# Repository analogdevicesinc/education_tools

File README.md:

# ADI Educational Content

[Analog Devices Inc.](https://www.analog.com/en/index.html)

Resource files for applications/examples with Active Learning Modules [ADALM1000](https://www.analog.com/en/design-center/evaluation-hardware-and-software/evaluation-boards-kits/adalm1000.html), [ADALM2000](https://www.analog.com/en/design-center/evaluation-hardware-and-software/evaluation-boards-kits/adalm2000.html), [ADALM-PLUTO](https://www.analog.com/en/design-center/evaluation-hardware-and-software/evaluation-boards-kits/adalm-pluto.html) and [ADALP2000](https://www.analog.com/en/design-center/evaluation-hardware-and-software/evaluation-boards-kits/EVAL-ADALP2000.html) Parts Kit.

Most of the files are linked as archives to the activities available in the [Analog Devices Engineering University Program](https://wiki.analog.com/university).

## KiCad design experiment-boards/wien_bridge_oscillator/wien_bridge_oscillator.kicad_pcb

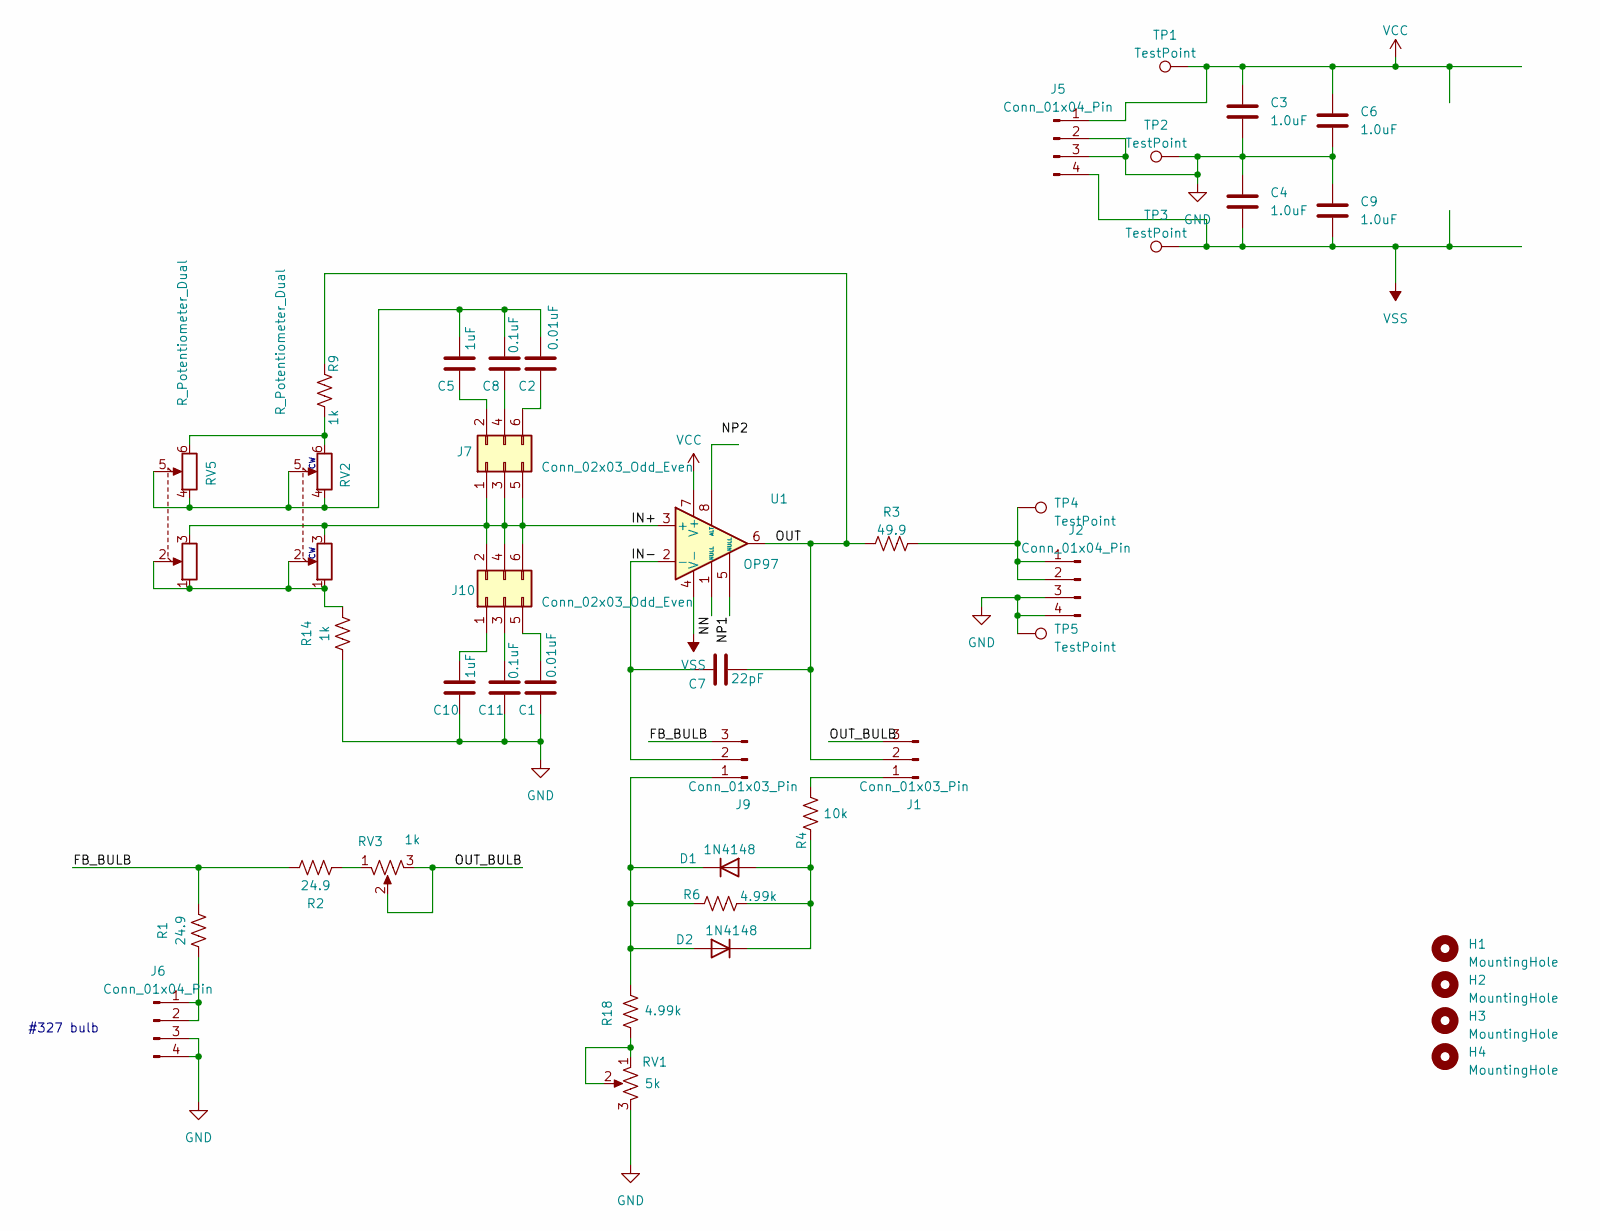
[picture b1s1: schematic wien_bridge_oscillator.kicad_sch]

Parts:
C1, C2: 0.01uF; C_Rect_L7.0mm_W3.5mm_P2.50mm_P5.00mm
C3, C4, C6, C9: 1.0uF; C_Rect_L7.0mm_W3.5mm_P2.50mm_P5.00mm
C5, C10: 1uF; C_Rect_L7.0mm_W3.5mm_P2.50mm_P5.00mm
C7: 22pF; C_Rect_L7.0mm_W3.5mm_P2.50mm_P5.00mm
C8, C11: 0.1uF; C_Rect_L7.0mm_W3.5mm_P2.50mm_P5.00mm
D1, D2: 1N4148; D_DO-35_SOD27_P7.62mm_Horizontal
H1, H2, H3, H4: MountingHole; MountingHole_3.2mm_M3
J1, J9: Conn_01x03_Pin; PinHeader_1x03_P2.54mm_Vertical
J2, J5, J6: Conn_01x04_Pin; PinHeader_1x04_P2.54mm_Vertical
J7, J10: Conn_02x03_Odd_Even; PinHeader_2x03_P2.54mm_Vertical
R1, R2: 24.9; R_Axial_DIN0207_L6.3mm_D2.5mm_P10.16mm_Horizontal
R3: 49.9; R_Axial_DIN0207_L6.3mm_D2.5mm_P10.16mm_Horizontal
R4: 10k; R_Axial_DIN0207_L6.3mm_D2.5mm_P10.16mm_Horizontal
R6, R18: 4.99k; R_Axial_DIN0207_L6.3mm_D2.5mm_P10.16mm_Horizontal
R9, R14: 1k; R_Axial_DIN0207_L6.3mm_D2.5mm_P10.16mm_Horizontal
RV1: 5k; Potentiometer_Bourns_3386F_Vertical
RV2: R_Potentiometer_Dual; Potentiometer_Bourns_3386F_Vertical
RV3: 1k; Potentiometer_Bourns_3386F_Vertical
RV5: R_Potentiometer_Dual; Potentiometer_Bourns_PRS12R-4x_Dual_Vertical
TP1, TP2, TP3, TP4, TP5: TestPoint; TestPoint_Keystone_5005-5009_Compact
U1: OP97; DIP-8_W7.62mm

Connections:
/FB_BULB: J9.3, R1.2, R2.2
/IN+: J7.1, J7.3, J7.5, J10.2, J10.4, J10.6, RV2.3, RV5.3, U1.3 (+)
/IN-: C7.1, J9.2, U1.2 (-)
/NN: U1.1 (NULL)
/NP1: U1.5 (NULL)
/OUT: C7.2, J1.2, R3.1, R9.1, U1.6
/OUT_BULB: J1.3, RV3.2, RV3.3
GND: C1.1, C3.2, C4.1, C6.2, C9.1, C10.1, C11.1, J2.3, J2.4, J5.2, J5.3, J6.3, J6.4, R14.1, RV1.3, TP2.1, TP5.1
unnamed: C2.2, C5.2, C8.2, RV2.4, RV2.5, RV5.4, RV5.5
unnamed: D1.2 (A), D2.1 (K), R4.1, R6.2
unnamed: D1.1 (K), D2.2 (A), J9.1, R6.1, R18.2
unnamed: J1.1, R4.2
unnamed: J2.1, J2.2, R3.2, TP4.1
unnamed: J6.1, J6.2, R1.1
unnamed: C5.1, J7.2
unnamed: C8.1, J7.4
unnamed: C2.1, J7.6
unnamed: C10.2, J10.1
unnamed: C11.2, J10.3
unnamed: C1.2, J10.5
unnamed: R2.1, RV3.1
unnamed: R9.2, RV2.6, RV5.6
unnamed: R14.2, RV2.1, RV2.2, RV5.1, RV5.2
unnamed: R18.1, RV1.1, RV1.2
VCC: C3.1, C6.1, J5.1, TP1.1, U1.7 (V+)
VSS: C4.2, C9.2, J5.4, TP3.1, U1.4 (V-)

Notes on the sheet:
#327 bulb

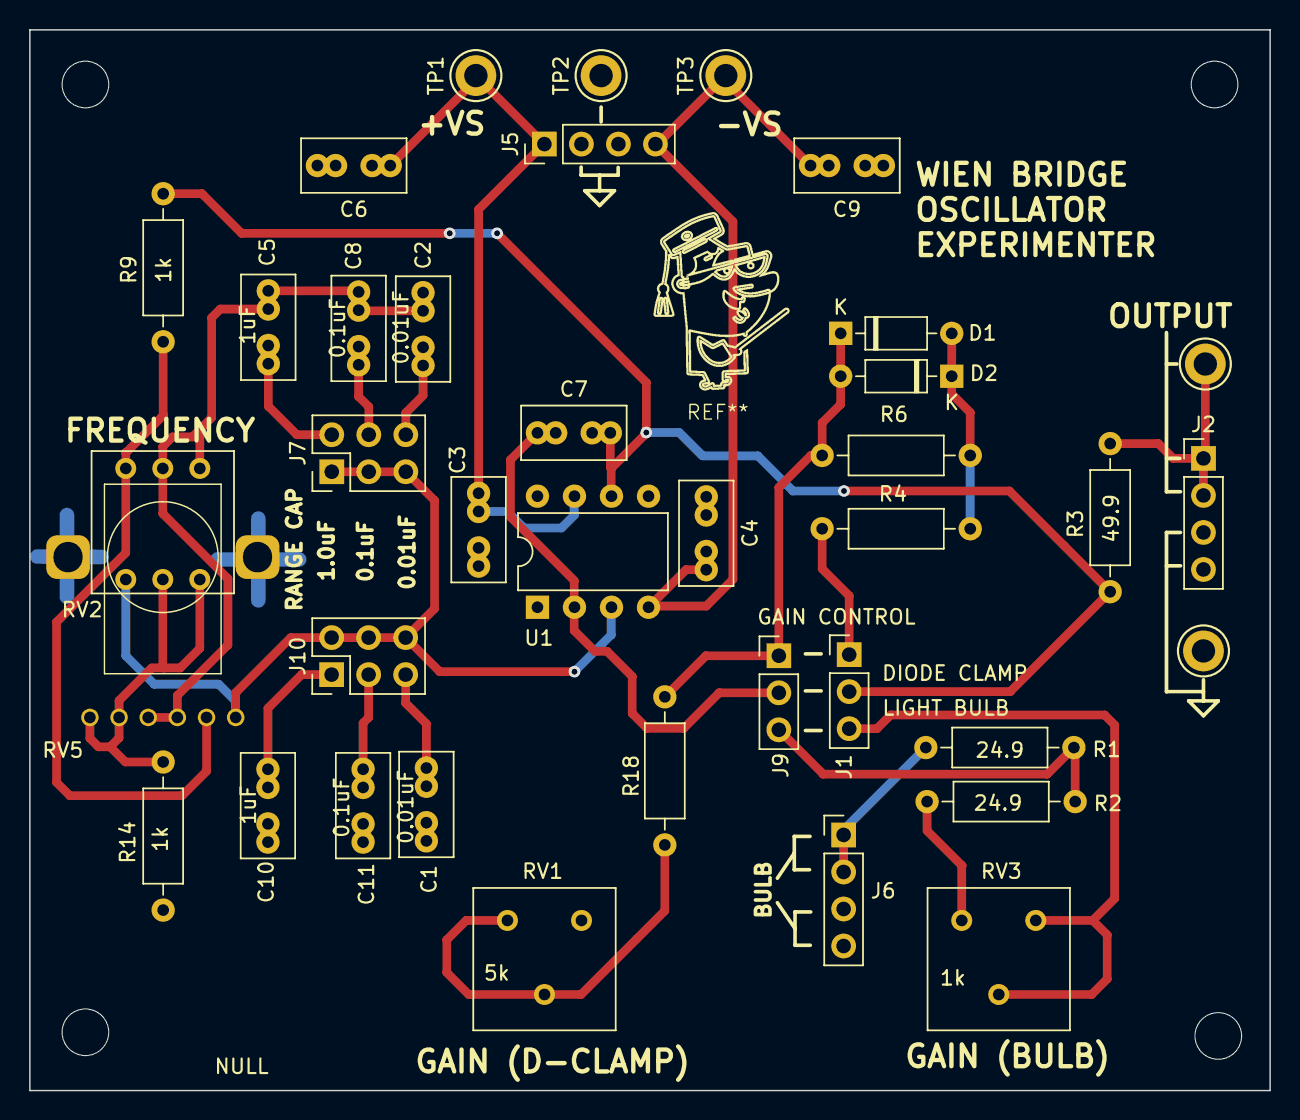
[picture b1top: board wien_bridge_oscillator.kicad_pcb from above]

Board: 2 copper layers, 85.1 x 72.8 mm, 42 parts (0 on the bottom side), 24 nets.

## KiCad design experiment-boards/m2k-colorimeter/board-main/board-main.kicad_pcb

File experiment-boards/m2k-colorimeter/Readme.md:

# M2k Colorimeter Accessory Board

TODO colorimeter theory, usage

## PCBs

This project consists of 4 PCBs to be assembled:

1. The main board (`board-main/`), which plugs in to the m2k
2. The RGB LED riser board (`board-led/`). Depending on the configuration, one or two may be used.
3. The photodiode riser board (`board-photodiode/`). Two are required.
4. The cuvette holder board (`board-holder/`). One is required (mounted at the top). For additional support and alignment, another one may be mounted right on the main board. No electrical function, just mechanical. Adapted from the [CN0363
](https://analog.com/CN0363).

Each board has gerber and drill files in `board-.../gerbers` and also a PDF in this root folder.

TODO insert images of each of the boards, assembly diagrams.

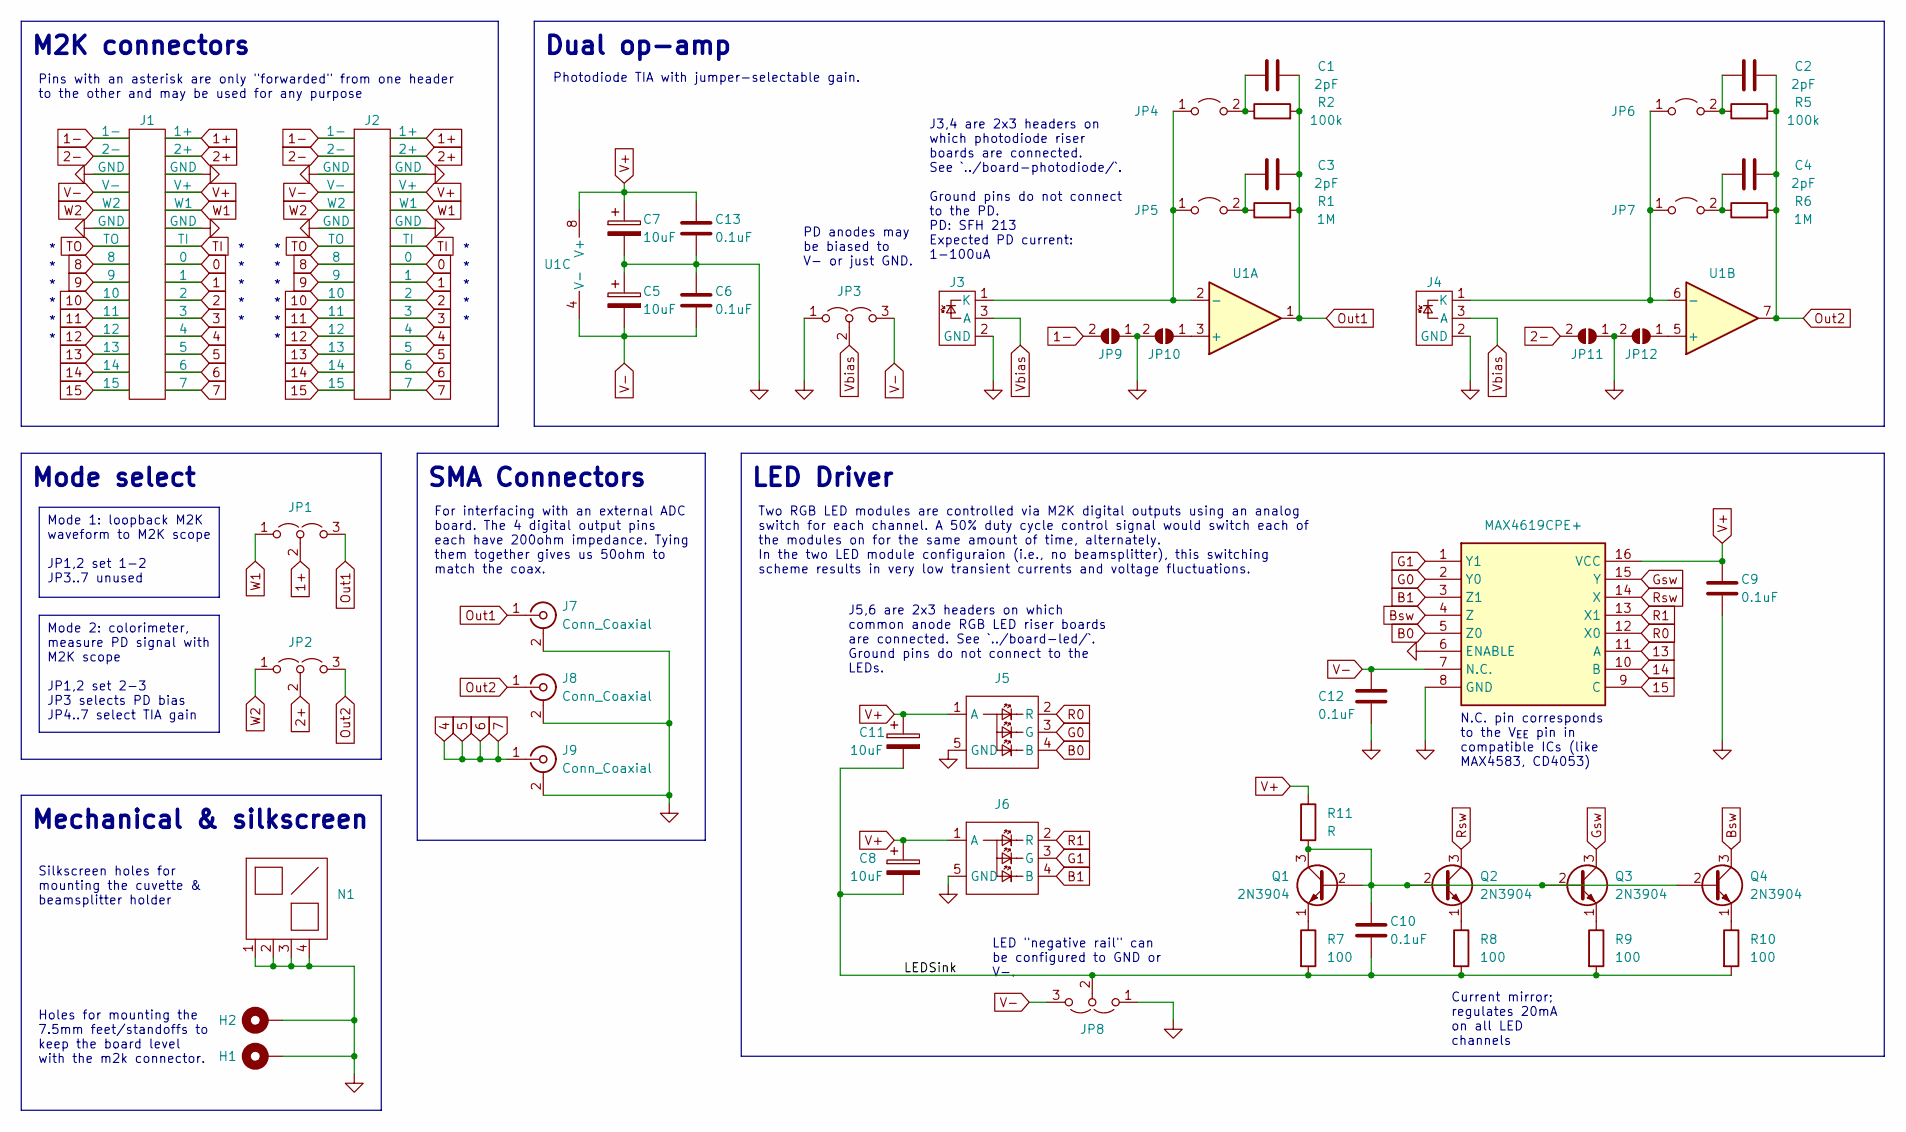
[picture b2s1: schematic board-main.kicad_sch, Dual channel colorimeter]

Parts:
C1, C2, C3, C4: 2pF; C_Disc_D6.0mm_W2.5mm_P5.00mm
C5, C7, C8, C11: 10uF; CP_Radial_D8.0mm_P3.50mm
C6, C9, C10, C12, C13: 0.1uF; C_Disc_D5.1mm_W3.2mm_P5.00mm
H1, H2: MountingHole_Pad; MountingHole_3mm_Pad
J1: Full15_Female; PinSocket_2x15_P2.54mm_Vertical
J2: Full15_Male; PinHeader_2x15_P2.54mm_Vertical
J3, J4: PhotodiodeRiser
J5, J6: LEDRiser
J7, J8, J9: Conn_Coaxial; SMA_Amphenol_132289_EdgeMount
JP1, JP2, JP3, JP8: Jumper_3_Open; PinHeader_1x03_P2.54mm_Vertical
JP4, JP5, JP6, JP7: Jumper_2_Open; PinHeader_1x02_P2.54mm_Vertical
JP9, JP10, JP11, JP12: 0; SolderJumper-2_P1.3mm_Open_RoundedPad1.0x1.5mm
N1: CuvetteHolder; CuvetteHolderDiagram
Q1, Q2, Q3, Q4: 2N3904; TO-92_HandSolder
R1, R6: 1M; R_Axial_DIN0207_L6.3mm_D2.5mm_P10.16mm_Horizontal
R2, R5: 100k; R_Axial_DIN0207_L6.3mm_D2.5mm_P10.16mm_Horizontal
R7, R8, R9, R10: 100; R_Axial_DIN0207_L6.3mm_D2.5mm_P10.16mm_Horizontal
R11: R; R_Axial_DIN0207_L6.3mm_D2.5mm_P10.16mm_Horizontal
U1: DIP-8_W7.62mm_Socket_LongPads
U2: MAX4619CPE+; DIP-16_W7.62mm_LongPads; Mouser Part Number 700-MAX4619CPE

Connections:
0: J1.15 (0), J2.15 (0)
1: J1.13 (1), J2.13 (1)
1+: J1.29 (1+), J2.29 (1+), JP1.2 (C)
1-: J1.30 (1-), J2.30 (1-), JP9.2 (B)
2: J1.11 (2), J2.11 (2)
2+: J1.27 (2+), J2.27 (2+), JP2.2 (C)
2-: J1.28 (2-), J2.28 (2-), JP11.2 (B)
3: J1.9 (3), J2.9 (3)
4: J1.1 (7), J1.3 (6), J1.5, J1.7 (4), J2.1 (7), J2.3 (6), J2.5, J2.7 (4), J9.1 (In)
8: J1.16 (8), J2.16 (8)
9: J1.14 (9), J2.14 (9)
10: J1.12 (10), J2.12 (10)
11: J1.10 (11), J2.10 (11)
12: J1.8 (12), J2.8 (12)
13: J1.6 (13), J2.6 (13), U2.11 (A)
14: J1.4 (14), J2.4 (14), U2.10 (B)
15: J1.2 (15), J2.2 (15), U2.9 (C)
/LEDSink: C8.2, C10.2, C11.2, JP8.2 (C), R7.2, R8.2, R9.2, R10.2
B0: J5.4 (B), U2.5 (Z0)
B1: J6.4 (B), U2.3 (Z1)
Bsw: Q4.3 (C), U2.4 (Z)
G0: J5.3 (G), U2.2 (Y0)
G1: J6.3 (G), U2.1 (Y1)
GND: C5.1, C6.1, C7.2, C9.2, C12.2, C13.2, H1.1, H2.1, J1.19 (GND), J1.20 (GND), J1.25 (GND), J1.26 (GND), J2.19 (GND), J2.20 (GND), J2.25 (GND), J2.26 (GND), J3.2 (GND), J4.2 (GND), J5.5 (GND), J6.5 (GND), J7.2 (Ext), J8.2 (Ext), J9.2 (Ext), JP3.1 (A), JP8.1 (A), JP9.1 (A), JP10.2 (B), JP11.1 (A), JP12.2 (B), N1.1, N1.2, N1.3, N1.4, U2.6 (ENABLE), U2.8 (GND)
Gsw: Q3.3 (C), U2.15 (Y)
unnamed: J3.1 (K), JP4.1 (A), JP5.1 (A), U1.2 (-)
unnamed: J4.1 (K), JP6.1 (A), JP7.1 (A), U1.6 (-)
unnamed: C1.1, JP4.2 (B), R2.1
unnamed: C3.1, JP5.2 (B), R1.1
unnamed: C2.1, JP6.2 (B), R5.1
unnamed: C4.1, JP7.2 (B), R6.1
unnamed: JP10.1 (A), U1.3 (+)
unnamed: JP12.1 (A), U1.5 (+)
unnamed: C10.1, Q1.2 (B), Q1.3 (C), Q2.2 (B), Q3.2 (B), Q4.2 (B), R11.2
unnamed: Q1.1 (E), R7.1
unnamed: Q2.1 (E), R8.1
unnamed: Q3.1 (E), R9.1
unnamed: Q4.1 (E), R10.1
Out1: C1.2, C3.2, J7.1 (In), JP1.3 (B), R1.2, R2.2, U1.1
Out2: C2.2, C4.2, J8.1 (In), JP2.3 (B), R5.2, R6.2, U1.7
R0: J5.2 (R), U2.12 (X0)
R1: J6.2 (R), U2.13 (X1)
Rsw: Q2.3 (C), U2.14 (X)
TI: J1.17 (TI), J2.17 (TI)
TO: J1.18 (TO), J2.18 (TO)
V+: C7.1, C8.1, C9.1, C11.1, C13.1, J1.23 (V+), J2.23 (V+), J5.1 (A), J6.1 (A), R11.1, U1.8 (V+), U2.16 (VCC)
V-: C5.2, C6.2, C12.1, J1.24 (V-), J2.24 (V-), JP3.3 (B), JP8.3 (B), U1.4 (V-), U2.7 (N.C.)
Vbias: J3.3 (A), J4.3 (A), JP3.2 (C)
W1: J1.21 (W1), J2.21 (W1), JP1.1 (A)
W2: J1.22 (W2), J2.22 (W2), JP2.1 (A)

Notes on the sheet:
Pins with an asterisk are only "forwarded" from one header to the other and may be used for any purpose
Holes for mounting the 7.5mm feet/standoffs to keep the board level with the m2k connector.
J3,4 are 2x3 headers on which photodiode riser boards are connected. See `../board-photodiode/`. Ground pins do not connect to the PD. PD: SFH 213 Expected PD current: 1-100uA
Mode 2: colorimeter, measure PD signal with M2K scope JP1,2 set 2-3 JP3 selects PD bias JP4..7 select TIA gain
For interfacing with an external ADC board. The 4 digital output pins each have 200ohm impedance. Tying them together gives us 50ohm to match the coax.
PD anodes may be biased to V- or just GND.
LED "negative rail" can be configured to GND or V-.
Mode 1: loopback M2K waveform to M2K scope JP1,2 set 1-2 JP3..7 unused
Two RGB LED modules are controlled via M2K digital outputs using an analog switch for each channel. A 50% duty cycle control signal would switch each of the modules on for the same amount of time, alternately. In the two LED module configuraion (i.e., no beamsplitter), this switching scheme results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
N.C. pin corresponds to the V_{EE} pin in compatible ICs (like MAX4583, CD4053)
Current mirror; regulates 20mA on all LED channels
Silkscreen holes for mounting the cuvette & beamsplitter holder
J5,6 are 2x3 headers on which common anode RGB LED riser boards are connected. See `../board-led/`. Ground pins do not connect to the LEDs.
Dual op-amp
LED Driver
Mode select
Photodiode TIA with jumper-selectable gain.
M2K connectors
Mechanical & silkscreen
SMA Connectors

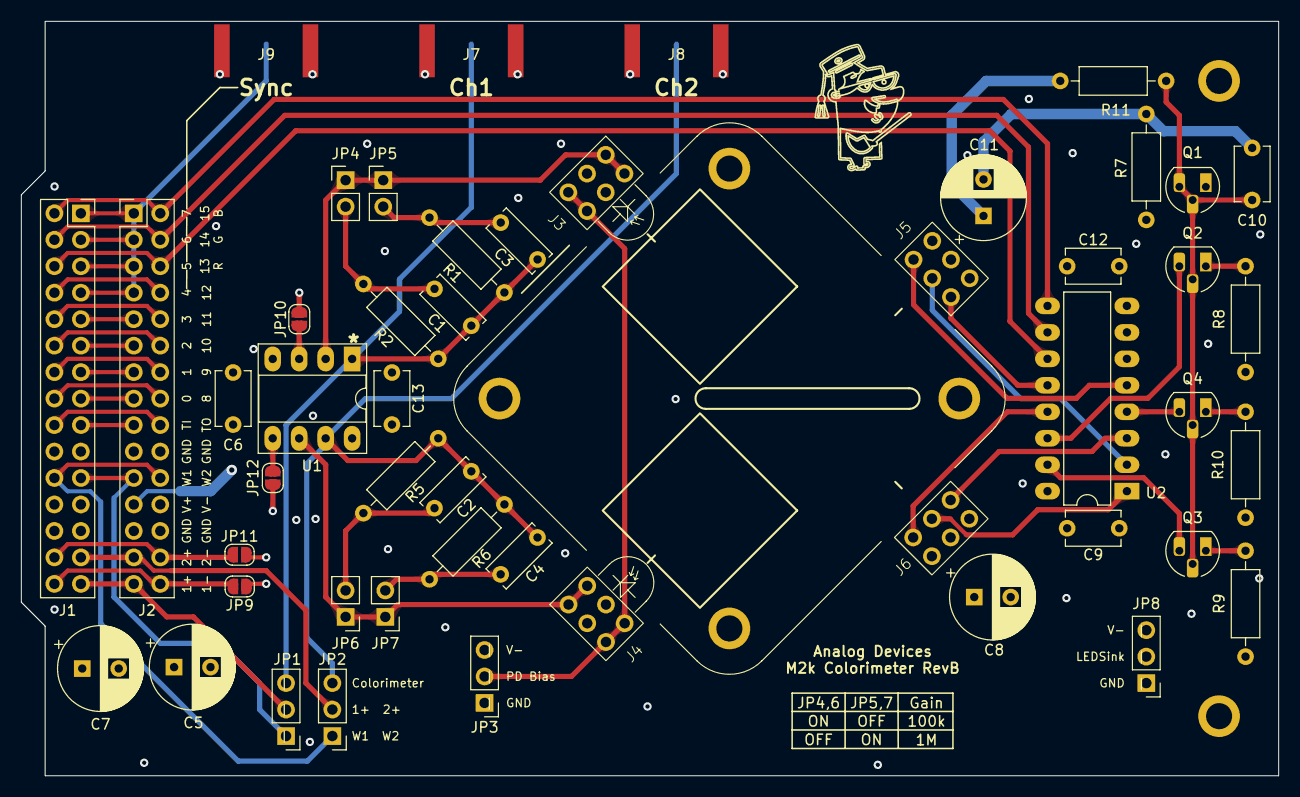
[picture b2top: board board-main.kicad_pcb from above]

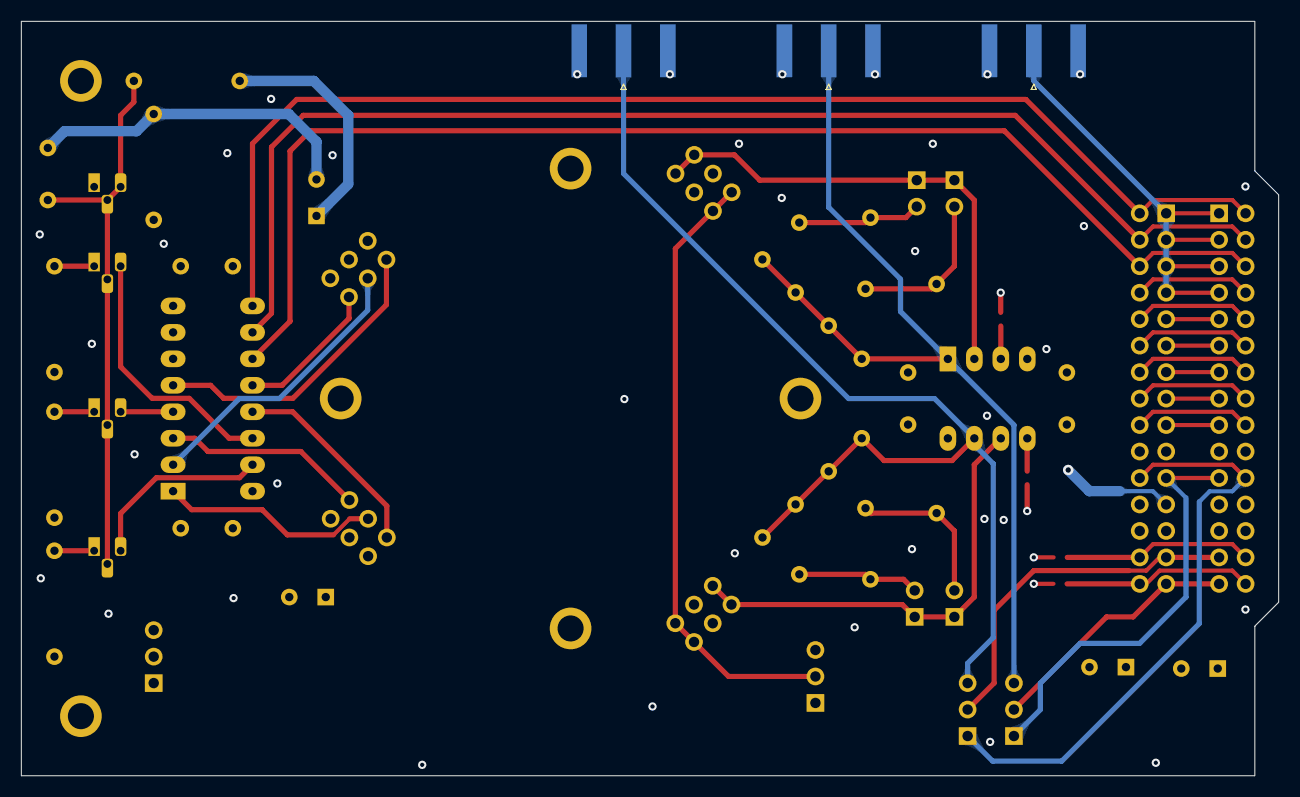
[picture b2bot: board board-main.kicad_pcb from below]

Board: 4 copper layers, 120.6 x 72.4 mm, 52 parts (3 on the bottom side), 50 nets.

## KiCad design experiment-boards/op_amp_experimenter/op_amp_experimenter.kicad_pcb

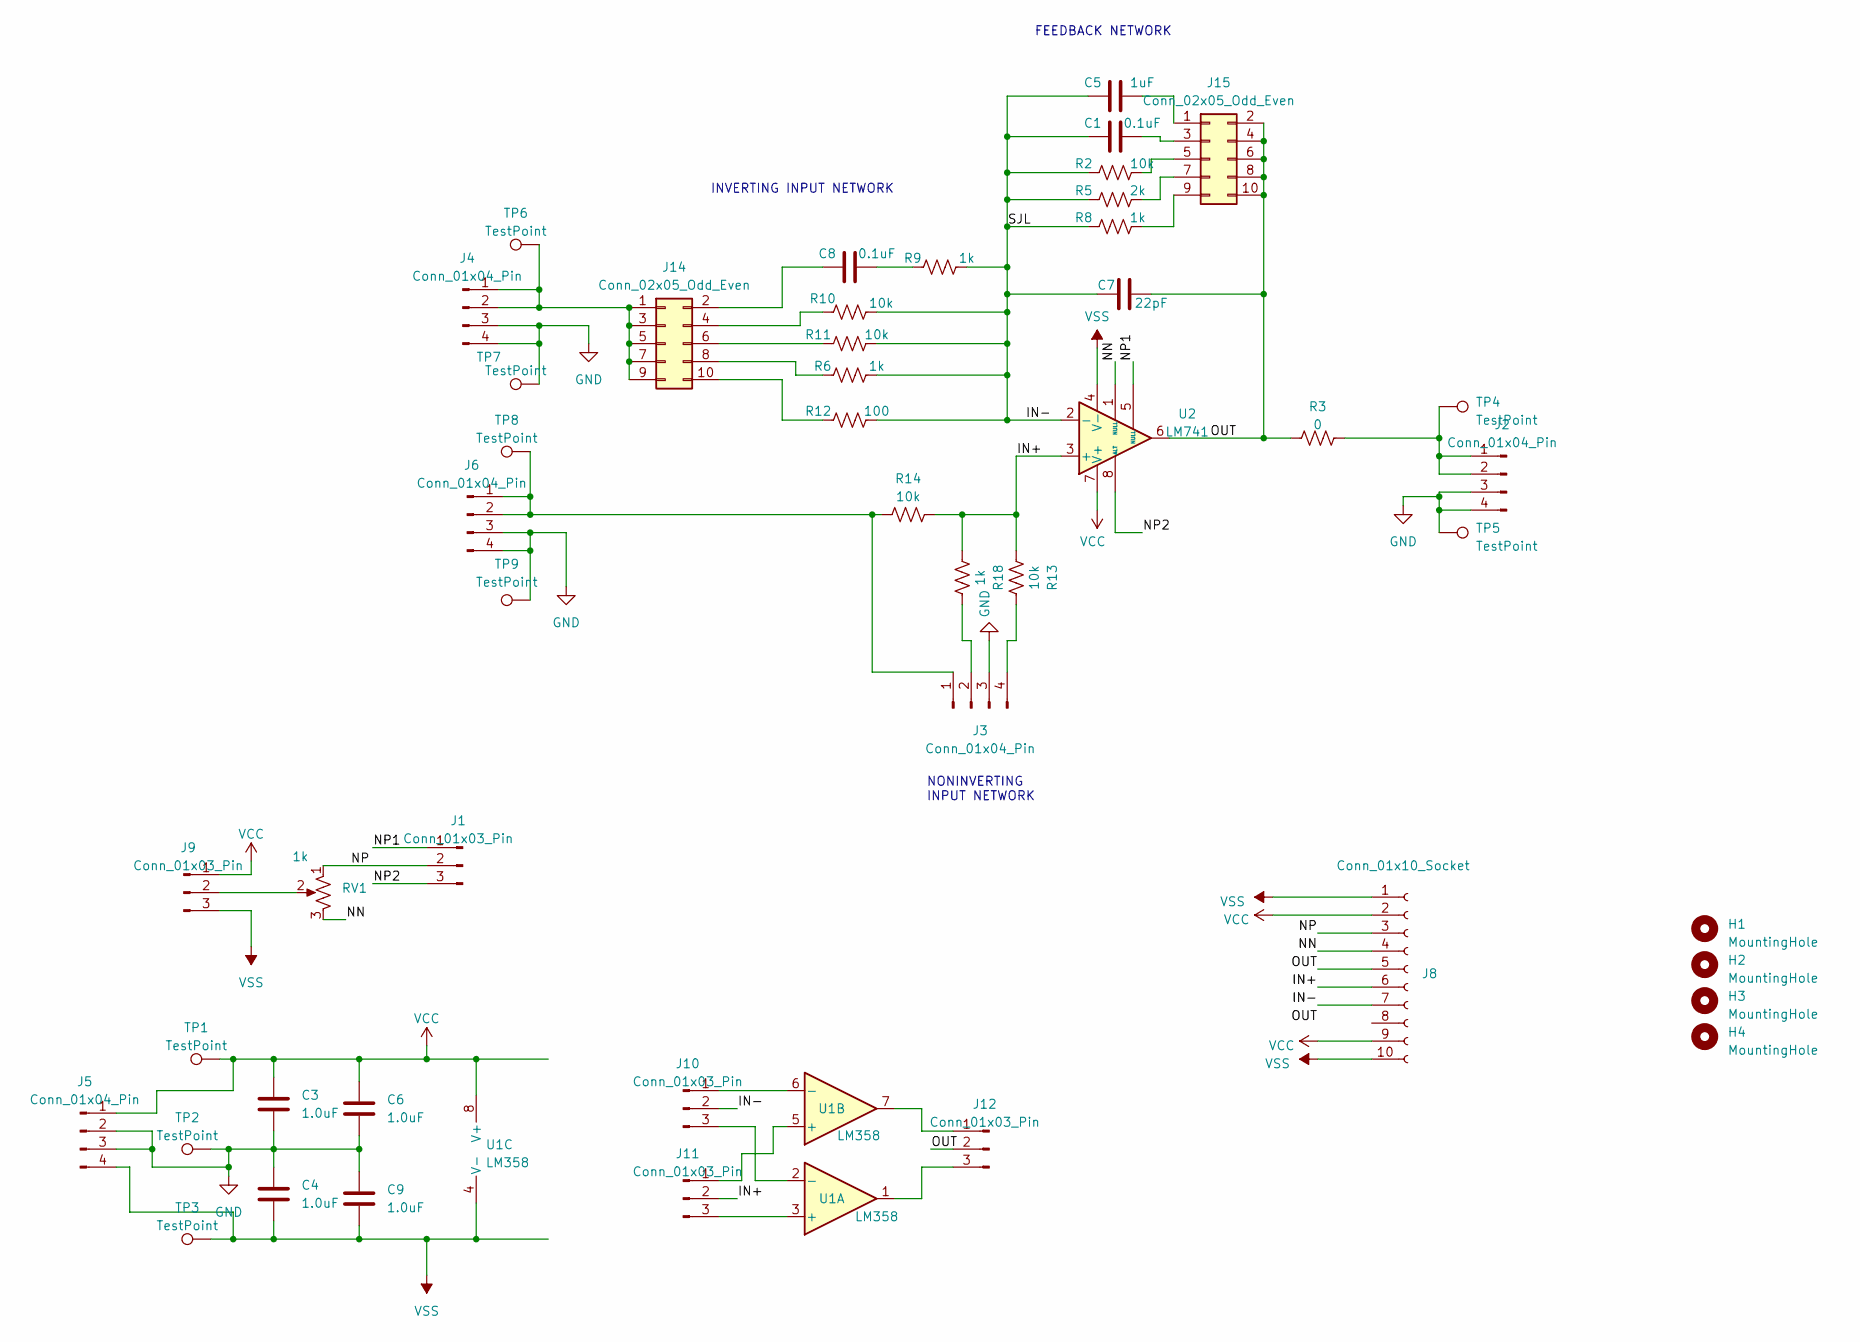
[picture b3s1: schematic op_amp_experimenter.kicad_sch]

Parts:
C1, C8: 0.1uF; C_Rect_L9.0mm_W3.2mm_P7.50mm_MKT
C3, C4, C6, C9: 1.0uF; C_Rect_L9.0mm_W3.2mm_P7.50mm_MKT
C5: 1uF; C_Rect_L9.0mm_W3.2mm_P7.50mm_MKT
C7: 22pF; C_Rect_L9.0mm_W3.2mm_P7.50mm_MKT
H1, H2, H3, H4: MountingHole; MountingHole_3.2mm_M3
J1, J9, J10, J11, J12: Conn_01x03_Pin; PinHeader_1x03_P2.54mm_Vertical
J2, J3, J4, J5, J6: Conn_01x04_Pin; PinHeader_1x04_P2.54mm_Vertical
J8: Conn_01x10_Socket; PinSocket_1x10_P2.54mm_Vertical
J14, J15: Conn_02x05_Odd_Even; PinHeader_2x05_P2.54mm_Vertical
R2, R10, R11, R13, R14: 10k; R_Axial_DIN0207_L6.3mm_D2.5mm_P10.16mm_Horizontal
R3: 0; R_Axial_DIN0207_L6.3mm_D2.5mm_P10.16mm_Horizontal
R5: 2k; R_Axial_DIN0207_L6.3mm_D2.5mm_P10.16mm_Horizontal
R6, R8, R9, R18: 1k; R_Axial_DIN0207_L6.3mm_D2.5mm_P10.16mm_Horizontal
R12: 100; R_Axial_DIN0207_L6.3mm_D2.5mm_P10.16mm_Horizontal
RV1: 1k; Potentiometer_Bourns_3386F_Vertical
TP1, TP2, TP3, TP4, TP5, TP6, TP7, TP8, TP9: TestPoint; TestPoint_Keystone_5005-5009_Compact
U1: LM358; DIP-8_W7.62mm_LongPads
U2: LM741; DIP-8_W7.62mm

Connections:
/IN+: J8.6, J11.2, R13.1, R14.2, R18.1, U2.3 (+)
/IN-: C1.1, C5.1, C7.1, J8.7, J10.2, R2.1, R5.1, R6.2, R8.1, R9.2, R10.2, R11.2, R12.2, U2.2 (-)
/NN: J8.4, RV1.3, U2.1 (NULL)
/NP: J1.2, J8.3, RV1.1
/NP1: J1.1, U2.5 (NULL)
/NP2: J1.3, U2.8 (ALT)
/OUT: C7.2, J8.5, J12.2, J15.2, J15.4, J15.6, J15.8, J15.10, R3.1, U2.6
GND: C3.2, C4.1, C6.2, C9.1, J2.3, J2.4, J3.3, J4.3, J4.4, J5.2, J5.3, J6.3, J6.4, TP2.1, TP5.1, TP7.1, TP9.1
unnamed: C8.2, R9.1
unnamed: J2.1, J2.2, R3.2, TP4.1
unnamed: J3.1, J6.1, J6.2, R14.1, TP8.1
unnamed: J3.2, R18.2
unnamed: J3.4, R13.2
unnamed: J9.2, RV1.2
unnamed: J10.1, U1.6 (-)
unnamed: J10.3, U1.2 (-)
unnamed: J11.1, U1.5 (+)
unnamed: J11.3, U1.3 (+)
unnamed: J12.1, U1.7
unnamed: J12.3, U1.1
unnamed: J4.1, J4.2, J14.1, J14.3, J14.5, J14.7, J14.9, TP6.1
unnamed: C8.1, J14.2
unnamed: J14.4, R10.1
unnamed: J14.6, R11.1
unnamed: J14.8, R6.1
unnamed: J14.10, R12.1
unnamed: C5.2, J15.1
unnamed: C1.2, J15.3
unnamed: J15.5, R2.2
unnamed: J15.7, R5.2
unnamed: J15.9, R8.2
VCC: C3.1, C6.1, J5.1, J8.2, J8.9, J9.1, TP1.1, U1.8 (V+), U2.7 (V+)
VSS: C4.2, C9.2, J5.4, J8.1, J8.10, J9.3, TP3.1, U1.4 (V-), U2.4 (V-)

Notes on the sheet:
NONINVERTING INPUT NETWORK
FEEDBACK NETWORK
INVERTING INPUT NETWORK

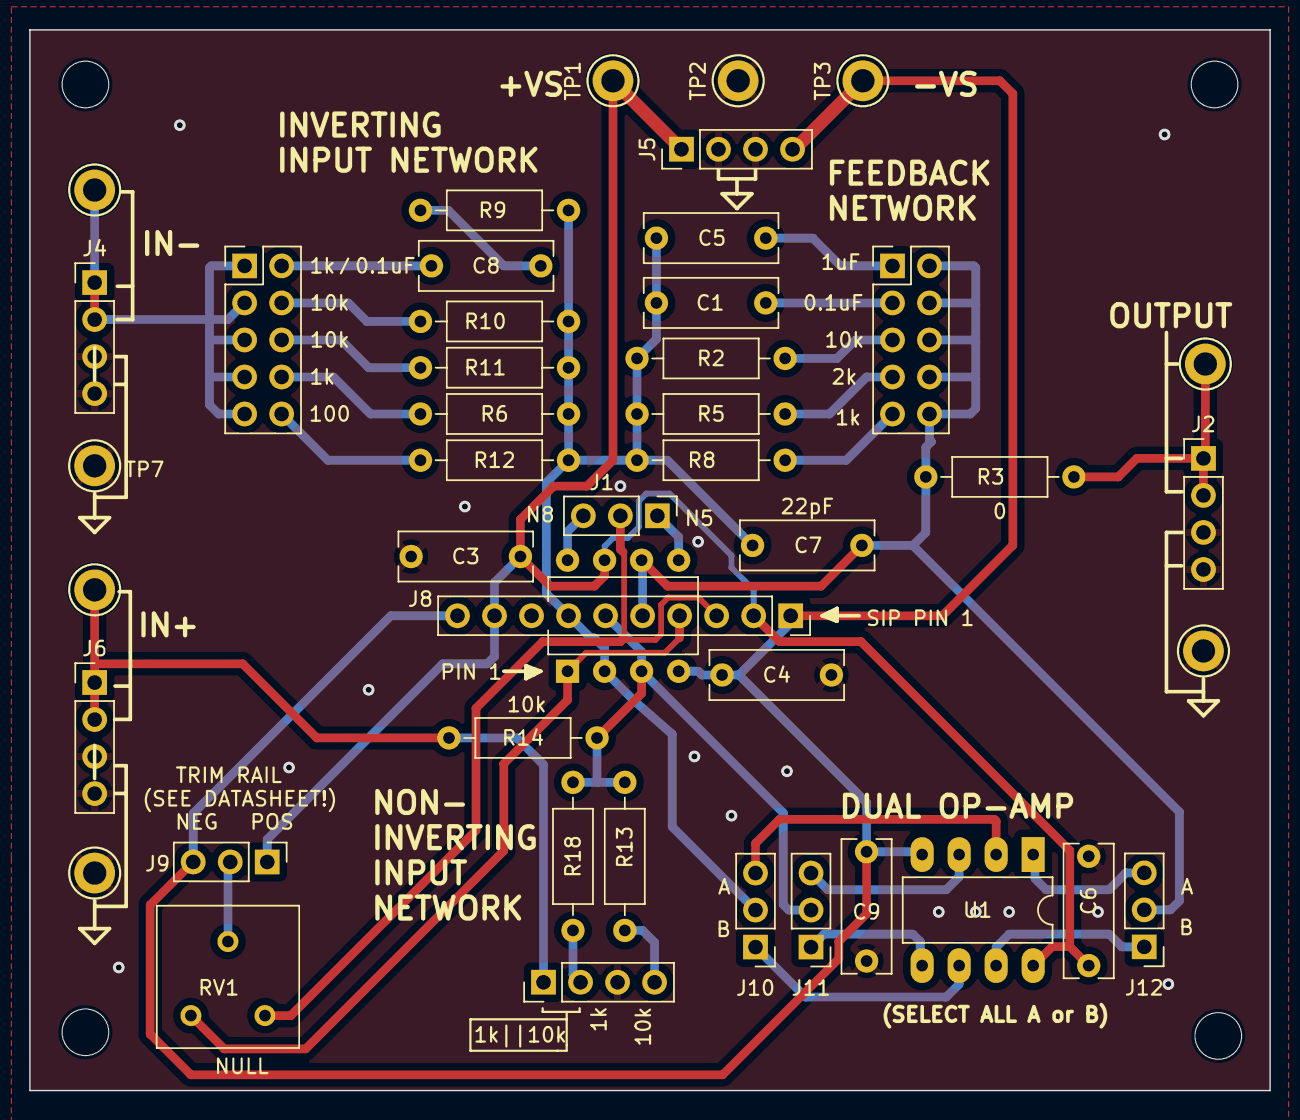
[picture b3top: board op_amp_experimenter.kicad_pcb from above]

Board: 2 copper layers, 85.1 x 72.8 mm, 49 parts (0 on the bottom side), 33 nets.

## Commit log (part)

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2018-10-24 Initial commit: add README.md
2018-10-24 m1k: add ADISimPE files
2018-10-24 m1k: add LTSpice files
2018-10-25 m1k: add LTSpice files for ADALM1000 Labs
2018-10-26 m2k: add ltspice files for diode activities
2018-10-26 m2k: add fritzing files for several m2k labs
2018-10-26 m2k: add ltspice file for voltage dependent cap
2018-10-29 m2k: change opamps to increase simulation speed
2018-10-30 m2k: add ltspice files for adc lab
2018-10-30 m2k: add ltspice files for switched cap lab
2018-10-30 m2k: add script file for buck converter lab
2018-10-31 m2k: add m2k connections in ltspice files
2018-11-01 m2k: add ltspice files for bjt as diode lab
2018-11-01 m2k: add adisimpe files
2018-11-08 m2k: add fritzing files for bjt curve lab
2018-11-09 m2k: add fritzing files for transformers lab
2018-11-23 m2k: add ltspice file for shunt regulator lab
2018-11-23 m2k: ltspice: nmos curve lab
2018-11-23 m2k: ltspice: bjt curver lab
2018-11-23 m2k: fritzing: common source amplifier lab
2018-11-23 m2k: fritzing: common emitter lab
2018-11-23 m2k: ltspice: amplifier output stages
2018-11-27 m2k: fritzing: add bjt as diode
2018-11-27 m2k: fritzing: add nmos as diode
2018-11-29 m2k: fritzing: bjt current mirror
2018-11-29 m2k: fritzing: differential temp sensor
2018-11-29 m2k: fritzing: shunt voltage regulator
2018-11-29 m2k: fritzing: simple op amp
2018-12-07 m2k: fritzing: add bjt emitter
2018-12-07 m2k: fritzing: add bjt stab current source
2018-12-07 m2k: fritzing: add bjt zero gain amp
2018-12-07 m2k: fritzing: mos zero gain amp
2018-12-07 m2k: fritzing: output stages
2018-12-10 m2k: ltspice: add efficency_power_loss
2018-12-14 m2k: fritzing: add adjustable external trigger
2018-12-14 m2k: fritzing: add cmos amplifier
2018-12-14 m2k: fritzing: add diff pair triangle to sine
2018-12-14 m2k: fritzing: add dac lab
2018-12-14 m2k: fritzing: add full op amp from blocks
2018-12-14 m2k: fritzing: add phase locked loop
2018-12-14 m2k: fritzing: add regulated voltage ref
2018-12-18 m2k: ltspice: eff pwr loss: fix power res value
2018-12-18 m2k: fritzing: add eff pwr loss bb
2018-12-19 m2k: fritzing: add negative voltage reference lab
2018-12-19 m2k: ltspice: initial active filter circuits
2019-01-07 m1k: fritzing: add impedance measurement bb
2019-01-22 m1k: ltspice: loudspeaker impedance
2019-01-22 m2k: fritzing: loudspeaker impedance
2019-01-22 m2k: ltspice: bjt emitter ff
2019-01-22 m2k: ltspice: bjt stab curr source
2019-01-22 m2k: ltspice: mos diff pair
2019-01-22 m2k: ltspice: mos zero gain amp
2019-01-22 m2k: ltspice: trans input stage
2019-01-25 m2k: fritzing: mos stab cs
2019-01-25 m2k: fritzing: ttl inv and nand
2019-01-25 m2k: ltspice: cmos analog sw
2019-01-25 m2k: ltspice: output stages
2019-01-25 m2k: ltspice: silicon ctrl rect
2019-01-25 m2k: fritzing: output stages rename
2019-02-01 m2k: ltspice: bjt current mirror
2019-02-01 m2k: ltspice: cmos amplifier
2019-02-01 m2k: ltspice: comm emit amp
2019-02-01 m2k: fritzing: bjt multivibrator
2019-02-01 m2k: fritzing: cmos trans gate xor
2019-02-01 m2k: fritzing: mos current mirror
2019-02-08 m2k: fritzing: mos source follower
2019-02-08 m2k: ltspice: inductor self res + cmos trans gate
2019-02-08 m2k: ltspice: float current source
2019-02-08 m2k: ltspice: tuned amp 2
2019-02-14 m1k: ltspice: basic opamp config
2019-02-15 m2k: ltspice: cmos dtyle latch
2019-02-15 m2k: ltspice: nmos multivibrator
2019-03-01 m2k: ltspice: temp_ctrl_window_comp
2019-03-01 m2k: ltspice: update folder names
2019-03-04 m2k: frtzing: peltz oscillator
2019-03-04 m2k: fritzing: pulsed oscillator
2019-03-04 m2k: ltspice: nmos current mirror
2019-03-04 m2k: ltspice: led light sensor
2019-03-04 m2k: ltspice: pwm lab
2019-03-05 m2k: adisimpe: heartbeat circuit
2019-03-05 m2k: fritzing: heartbeat
2019-03-05 m2k: fritzing: buck
2019-03-11 m2k: ltspice: modify active filter circuits
2019-03-12 pluto: python: basic example
2019-03-12 pluto: python: add gen tx data example
2019-03-14 m2k: add import files for SG and PG
2019-03-27 m2k: ltspice: update dac schematic
2019-03-27 m2k: fritzing: add trans coupled amplifier
2019-03-27 m2k: ltspice: add ce loop gain
2019-03-27 m2k: ltspice: add colpitts osc
2019-03-27 m2k: ltspice: diff pair triangle to sine
2019-03-27 m2k: ltspice: add hartley osc
2019-03-27 m2k: ltspice: add polyphase filter
2019-03-27 m2k: ltspice: add transformer
2019-03-27 m2k: fritzing: add tuned amp p1
2019-04-15 m1k: ltspice: current sensing diff amp
2019-04-15 m1k: ltspice: vector summing amp
2019-04-15 m1k: fritzing: op amp bandwidth
2019-04-15 m1k: fritzing: vector summing amp
2019-04-16 m2k: fritzing: diode ring modulator
2019-04-17 m1k: fritzing: opamp open loop gain
2019-04-17 m1k: ltspice: difference amp
2019-04-26 m1k: fritzing: bjt as diode
2019-04-26 m1k: fritzing: difference amp
2019-04-26 m1k: ltspice: bjt as diode
2019-05-03 m1k: fritzing: bjt char curves
2019-05-03 m1k: fritzing: common source amplifier
2019-05-03 m1k: ltspice: bjt char curves
2019-05-03 m1k: ltspice: common source amplifier
2019-05-10 m1k: ltspice: dc-dc boost converters
2019-05-10 m1k: ltspice: diode rectifiers
2019-05-10 m1k: ltspice: voltage comparators
2019-05-10 m1k: fritzing: diode rectifiers
2019-05-10 m1k: fritzing: simple joule thief
2019-05-10 m1k: ltspice: bjt as switch
2019-05-10 m1k: ltspice: comm emit amp
2019-05-10 m1k: ltspice: nmos as switch
2019-05-10 m1k: fritzing: bjt as switch
2019-05-10 m1k: fritzing: comm emit amp
2019-05-10 m1k: fritzing: nmos as switch
2019-05-10 m1k: fritzing: nmos fet char curves
2019-05-20 m2k: ltspice: buck: fix short circuit
    Fix short circuit created by using duplicated labels
2019-07-04 m2k: import: add stairstep function
2019-07-10 m2k: ltspice: active_filters_ltspice:
    alpf_gain.asc title
    twint_notch.asc r3 1k
    adc_ltspice:
    dual_slope.asc DIO0
2019-07-12 m2k:other_resources:dual_slope_adc
    Files useful in Electronics II, Activity 4: Analog to Digital Conversion
2019-07-15 m2k: ltspice: pwm_lab_ltspice
    in pwm_carrier_ltspice.asc changed OP37 to OP07
2019-07-22 m2k: ltspice: active mixers
2019-07-26 m2k: ltspice: active_mixers_ltspice: LTC1043_ltspice
    added a new LTSpice file with the active mixer implemented with LTC1043
2019-07-29 m2k: ltspice: active_mixers_ltspice: DoubleBalanced_LTC1043_ltspice.asc
    LTSpice schematic for a double balanced active mixer implemented with LTC1043
2019-07-31 ps_noise_sniffer example that uses pyadi-iio
    This example has the same functionality as ps_noise_sniffer.py
    from power_supply_noise_sniffer_example but it uses pyadi-iio module which
    provides a convenient way to access and control ADI hardware
    from Python through existing IIO drivers.
2019-08-01 Update README.md
    Add information about ADALM-PLUTO applications and examples.
2019-08-01 README: minor edit
2019-08-01 m2k: fritzing: magnetic_proximity_sensor
    Fritzing files for Magnetic proximity sensor with AD22151
2019-08-07 m2k: fritzing: transient_response_RL_bb
    fritzing files for RL series circuit
2019-08-07 m2k: ltspice: transient_response_RC_ltspice
    LTspice schematic for RC series circuit
2019-08-07 m2k: ltspice: transient_response_RL_ltspice
    LTspice schematic for RL series circuit
2019-08-12 m2k: fritzing: transient_response_RL_bb
    Fritzing file for RL series circuit
2019-08-13 m2k: ltspice: lpf_hpf_ltspice
    LTSpice schematic of LPF and HPF circuits
2019-08-29 m2k: fritzing: bpf_bb
    Frizing file for Band pass filter activity
2019-08-29 m2k: ltspice: bsf_ltspice
    LTSpice schematic for the Band stop filter activity
2019-08-29 m2k: fritzing: bsf_bb
    Fritzing files for band stop filter actitvity
2019-08-29 m2k: ltspice: resonance_RLC_ltspice
    LTSpice schematic for RLC parallel circuit
2019-08-30 m2k: fritzing: cascaded_rc_bb
    Fritzing files for the activity Cascaded RC low pass filters
2019-09-06 m2k: fritzing: ohm_law_bb
    Fritzing file for Ohm's Law activity
2019-09-06 m2k: ltspice: loudspeaker_imp_ltspice
    LTspice schematics for Activity: Measuring a Loudspeaker Impedance Profile
2019-09-06 m2k: fritzing: loudspeaker_imp_bb
    Fritzing files for activity: Measuring a Loudspeaker Impedance Profile
2019-09-17 m2k: fritzing: IC_temperature_sensors_bb
    Fritzing files for the activity IC temperature sensors
2019-09-24 m2k: fritzing: adc_lab_bb: flash_adc-bb
    Modified fritzing file for Flash ADC
2019-09-24 m2k: ltspice: adc_ltspice: flash_adc
    Modified LTSpice schematic for Flash ADC
2019-09-24 m2k: fritzing: dac_bb: ad5626_bipolar_bb
    Fritzing file for AD5626 bipolar operation in Digital to analog conversion activity
2019-09-27 Add a license for this repo, and associated files.
2019-10-31 m2k: ltspice: comp: update comparator circuits
2019-10-31 m2k: fritzing: opamp_comp_bb: simple_comp-bb.fzz
    Added fritzing file for simple comparator circuit
2019-10-31 m2k: fritzing: opamp_comp_bb: non_inv_hys_com-bb
    Updated fritzing file for noninverting hysteresis comparator circuit
2019-10-31 m2k: fritzing: opamp_comp_bb: inv_hys_com-bb
    Updated fritzing file for inverting hysteresis comparator circuit
2019-10-31 m2k:ltspice:comp: minor fix
2019-11-20 m2k: ltspice: settling_time: update circuit
    Circuit rework + add potetiometer symbol
2019-12-13 m2k: fritzing: opamp_comp: update resistor values
2020-02-17 README: add product links
    Add links for ADALM1000, ADALM2000, ADALM-PLUTO and ADALP2000.
2020-02-25 m2k: fritzing: comm_emit_amp_bb: ce_amp_test_config-bb.fzz
    Modified Fritzing schematic
2020-03-31 m2k:ltspice:comm_emit_amp: adjust resistor value
    Adjust resistor values to reduce gain and avoid reaching circuit
    limitations.
2020-04-13 m2k: ltspice: freq_resp: update ltspice
2020-04-30 Initial release
    This is the inital release of the first 5 m1k accessory PC boards.
2020-05-29 Adding more board files
    Adding cad files for lumped LC trnasmission line board.
2020-06-28 Adding more board files
    Adding more accessory board files to the inventory
2021-01-28 Added fritzing files for Electre microphone lab activity
2021-04-16 README: update wiki links
    Use official wiki link for the ADI University Program.
2021-04-19 add more boards
    Design files etc. added for LTC1043 based analog mux board and adjustable pot voltagedivider board
2021-05-04 Adding lumped_and_dist_tlines.asc for transmission line lab
2021-05-29 Add some M2k boards
    Add CAD files for 2 M2k analog Mux boards and CAD files for M2k Breadboard adapter
2021-06-17 Initial commit of LTspice files for signal chain noise exercise Python refactoring / cleanup
2021-07-04 Initial Commit - Wien Bridge oscillator
2021-07-06 Adding LTspice files for transmission line lab
2021-07-06 Add LTspice files for Signal Chain Noise exercise
2021-07-06 Add python scripts for Signal Chain Noise exercise
2021-07-20 m2k: fritzing: heartrate: C2 polarity adjust
    Flip the capacitor C2 in the breadboard circuit to indicate the correct
    polarity.
2021-10-04 m2k:fritzing:cmos_amplif: fix part naming
2021-11-15 m2k:fritzing:cmos_analog_sw: fix part name
    Rename HEF4007 -> CD4007.
2022-06-24 m2k: cmos_logic_func: update part name
    Replace HEF4007 with CD4007 to allign with the actual naming of the
    hardware part.
2022-08-16 m2k: fritzing: xor gate fix part
    Replace HEF4007 wit CD4007.
2022-09-16 m2k: fritzing: pll: fix part name
    Replace HEF4007 with CD4007.
2023-03-23 m2k: fritzing: analog_trigger: rename part
    Rename HEF4007 -> CD4007.
2023-04-19 m2k: python: precision_adc_tutorial: aesthetics (comments, line styles, etc.) Default to ip:analog.local (works when run locally or remotely.)
2023-05-03 m2k: fritzing: ad22151: remove extra resistance
    Remove extra resitance value label.
2023-10-11 m2k: fritzing: transformer: update package
    Update the transformer package used in the breadboard circuit and use
    appropriate naming.
2023-12-01 Place circuit board design files under CC-BY-SA license.
2023-12-22 Add additional m1k, m2k accessory boards and experiment boards.
2024-08-22 Add the m2k's 50-ohm source termination
    Also adjust pulse generator timing. Waveforms don't match bench measurements otherwise.
2025-07-10 m2k: fritzing: simple op amps: fix wiring typo
    Channel 1 of the signal generator was incorrectly wired to the OP97.

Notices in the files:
experiment-boards/wien_bridge_oscillator/wien_bridge_oscillator.kicad_pcb:
CREATIVE COMMONS BY-SA
